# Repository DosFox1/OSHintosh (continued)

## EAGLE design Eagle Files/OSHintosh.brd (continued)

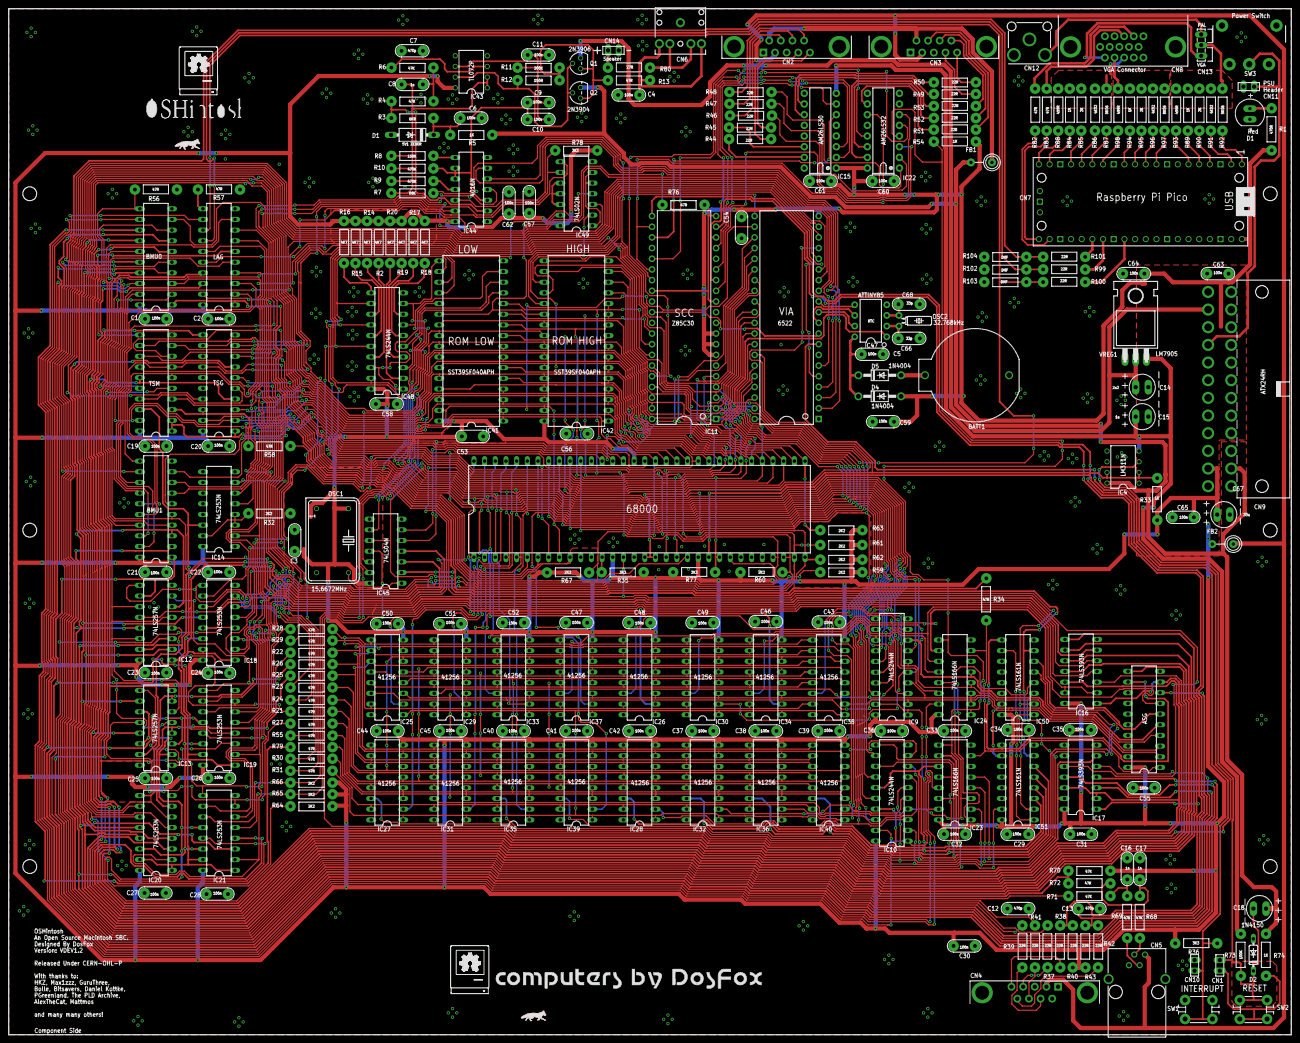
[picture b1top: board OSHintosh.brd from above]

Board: 2 copper layers, 305.0 x 244.0 mm, 252 parts (0 on the bottom side), 281 nets.

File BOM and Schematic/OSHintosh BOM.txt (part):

Partlist

Exported from OSHintosh v23.sch at 20/Mar/26 10:36

EAGLE Version 9.7.0 Copyright (c) 1988-2026 Autodesk, Inc.

Assembly variant: 

Part     Value                Device                       Package                      Library                 Sheet

BATT1                         BATTERY-20MM_PTH             BATTCOM_20MM_PTH             SparkFun-Batteries      1
C1       100n 50V             100N_TH_CAP                  CAP_5.08MM_PITCH             Capacitors TH           1
C2       100n 50V             100N_TH_CAP                  CAP_5.08MM_PITCH             Capacitors TH           1
C3       100n 50V             100N_TH_CAP                  CAP_5.08MM_PITCH             Capacitors TH           1
C4       100n 50V             100N_TH_CAP                  CAP_5.08MM_PITCH             Capacitors TH           1
C5       100n 50V             100N_TH_CAP                  CAP_5.08MM_PITCH             Capacitors TH           1
C6       100n 50V             100N_TH_CAP                  CAP_5.08MM_PITCH             Capacitors TH           1
C7       470p 50V             470P_TH_CAP                  CAP_5.08MM_PITCH             Capacitors TH           1
C8       1n 50V               1N_TH_CAP                    CAP_5.08MM_PITCH             Capacitors TH           1
C9       100n 50V             100N_TH_CAP                  CAP_5.08MM_PITCH             Capacitors TH           1
C10      100n 50V             100N_TH_CAP                  CAP_5.08MM_PITCH             Capacitors TH           1
C11      220p 50V             220P_TH_CAP                  CAP_5.08MM_PITCH             Capacitors TH           1
C12      470p 50V             470P_TH_CAP                  CAP_5.08MM_PITCH             Capacitors TH           1
C13      470p 50V             470P_TH_CAP                  CAP_5.08MM_PITCH             Capacitors TH           1
C14      2u2 50V              2U2_TH_ELEC_CAPVERTICAL      CAP_ELECTROLYTIC             Capacitors TH           1
C15      1u 50V               1U_TH_ELEC_CAPVERTICAL       CAP_ELECTROLYTIC             Capacitors TH           1
C16      1n 50V               1N_TH_CAP                    CAP_5.08MM_PITCH             Capacitors TH           1
C17      1n 50V               1N_TH_CAP                    CAP_5.08MM_PITCH             Capacitors TH           1
C18      4u7 50V              4U7_TH_ELEC_CAPVERTICAL      CAP_ELECTROLYTIC             Capacitors TH           1
C19      100n 50V             100N_TH_CAP                  CAP_5.08MM_PITCH             Capacitors TH           1
C20      100n 50V             100N_TH_CAP                  CAP_5.08MM_PITCH             Capacitors TH           1
C21      100n 50V             100N_TH_CAP                  CAP_5.08MM_PITCH             Capacitors TH           1
C22      100n 50V             100N_TH_CAP                  CAP_5.08MM_PITCH             Capacitors TH           1
C23      100n 50V             100N_TH_CAP                  CAP_5.08MM_PITCH             Capacitors TH           1
C24      100n 50V             100N_TH_CAP                  CAP_5.08MM_PITCH             Capacitors TH           1
C25      100n 50V             100N_TH_CAP                  CAP_5.08MM_PITCH             Capacitors TH           1
C26      100n 50V             100N_TH_CAP                  CAP_5.08MM_PITCH             Capacitors TH           1
C27      100n 50V             100N_TH_CAP                  CAP_5.08MM_PITCH             Capacitors TH           1
C28      100n 50V             100N_TH_CAP                  CAP_5.08MM_PITCH             Capacitors TH           1
C29      100n 50V             100N_TH_CAP                  CAP_5.08MM_PITCH             Capacitors TH           1
C30      100n 50V             100N_TH_CAP                  CAP_5.08MM_PITCH             Capacitors TH           1
C31      100n 50V             100N_TH_CAP                  CAP_5.08MM_PITCH             Capacitors TH           1
C32      100n 50V             100N_TH_CAP                  CAP_5.08MM_PITCH             Capacitors TH           1
C33      100n 50V             100N_TH_CAP                  CAP_5.08MM_PITCH             Capacitors TH           1
C34      100n 50V             100N_TH_CAP                  CAP_5.08MM_PITCH             Capacitors TH           1
C35      100n 50V             100N_TH_CAP                  CAP_5.08MM_PITCH             Capacitors TH           1
C36      100n 50V             100N_TH_CAP                  CAP_5.08MM_PITCH             Capacitors TH           1
C37      100n 50V             100N_TH_CAP                  CAP_5.08MM_PITCH             Capacitors TH           1
C38      100n 50V             100N_TH_CAP                  CAP_5.08MM_PITCH             Capacitors TH           1
C39      100n 50V             100N_TH_CAP                  CAP_5.08MM_PITCH             Capacitors TH           1
C40      100n 50V             100N_TH_CAP                  CAP_5.08MM_PITCH             Capacitors TH           1
C41      100n 50V             100N_TH_CAP                  CAP_5.08MM_PITCH             Capacitors TH           1
C42      100n 50V             100N_TH_CAP                  CAP_5.08MM_PITCH             Capacitors TH           1
C43      100n 50V             100N_TH_CAP                  CAP_5.08MM_PITCH             Capacitors TH           1
C44      100n 50V             100N_TH_CAP                  CAP_5.08MM_PITCH             Capacitors TH           1
C45      100n 50V             100N_TH_CAP                  CAP_5.08MM_PITCH             Capacitors TH           1
C46      100n 50V             100N_TH_CAP                  CAP_5.08MM_PITCH             Capacitors TH           1
C47      100n 50V             100N_TH_CAP                  CAP_5.08MM_PITCH             Capacitors TH           1
C48      100n 50V             100N_TH_CAP                  CAP_5.08MM_PITCH             Capacitors TH           1
C49      100n 50V             100N_TH_CAP                  CAP_5.08MM_PITCH             Capacitors TH           1
C50      100n 50V             100N_TH_CAP                  CAP_5.08MM_PITCH             Capacitors TH           1
C51      100n 50V             100N_TH_CAP                  CAP_5.08MM_PITCH             Capacitors TH           1
C52      100n 50V             100N_TH_CAP                  CAP_5.08MM_PITCH             Capacitors TH           1
C53      100n 50V             100N_TH_CAP                  CAP_5.08MM_PITCH             Capacitors TH           1
C54      100n 50V             100N_TH_CAP                  CAP_5.08MM_PITCH             Capacitors TH           1
C55      100n 50V             100N_TH_CAP                  CAP_5.08MM_PITCH             Capacitors TH           1
C56      100n 50V             100N_TH_CAP                  CAP_5.08MM_PITCH             Capacitors TH           1
C57      100n 50V             100N_TH_CAP                  CAP_5.08MM_PITCH             Capacitors TH           1
C58      100n 50V             100N_TH_CAP                  CAP_5.08MM_PITCH             Capacitors TH           1
C59      100n 50V             100N_TH_CAP                  CAP_5.08MM_PITCH             Capacitors TH           1
C60      100n 50V             100N_TH_CAP                  CAP_5.08MM_PITCH             Capacitors TH           1
C61      100n 50V             100N_TH_CAP                  CAP_5.08MM_PITCH             Capacitors TH           1
C62      100n 50V             100N_TH_CAP                  CAP_5.08MM_PITCH             Capacitors TH           1
C63      100n 50V             100N_TH_CAP                  CAP_5.08MM_PITCH             Capacitors TH           1
C64      100n 50V             100N_TH_CAP                  CAP_5.08MM_PITCH             Capacitors TH           1
C65      100n 50V             100N_TH_CAP                  CAP_5.08MM_PITCH             Capacitors TH           1
C66      33p                  33P_TH_CAP                   CAP_5.08MM_PITCH             Capacitors TH           1
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
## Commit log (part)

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2026-03-31 Create README.md
    Added intial readme for the OSHintosh
2026-03-31 Add files via upload
    Added initial files for the OSHintosh
2026-03-31 Add files via upload
    ffs github
2026-05-18 Add files via upload
    Added Rominator Files.
    Disk images incldue original Rominator disk image, the ROM disk from the Macintosh Classic, as well as the OSHintosh disk image.
    OSHINTOSH_HIGH and OSHINTOSH LOW are the ROM images for the OSHintosh onboard rominator.
2026-06-09 Update README.md
    Typos and made note about GALs
2026-06-09 Add files via upload
    added missing jed files after github ate my files >:(
